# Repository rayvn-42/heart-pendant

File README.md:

## Heart Pendant
> A two part PCB, one used as a bracelet that senses heart pulses, and a pendant shaped as a heart that shows them

---

### What is Heart Pendant?
Its a small wearable made of two boards on a single PCB, joined by a break-away joint, The square half is a bracelet that measures the pulse with a heartbeat sensor.The heart-shaped half is a necklace pendant that shows each beat as a light animation moving smoothly around a ring of addressable LEDs. Once you snap the halves apart, each one works on its own and they talk to each other wirelessly.

### Why is Heart Pendant useful?
Its not really useful :), but its just fun and a reminder that each second your heart beats :) or something. I mean its just cool.

---

### How it works?
The bracelet's ESP32-C3 reads a heartbeat sensor module and detects each beat. It sends the beat to the pendant using the ESP-NOW protocol. Then the pendants ESP32 displays that heartbeat as a simple rotational animation using the addressable LEDs. Each half has its own LiPo battery, USB C port with a dedicated charge controller, and a 3v3 regulator, so both can be charged and used separately.

### Schematic

## So far
- [x] Schematic: ESP32 core, USB-C input, charger, regulator, power switch, battery sensing
- [x] Pulse sensor and LED ring
- [x] PCB layout
- [x] Quote Component & PCB + Stencil Order
- [x] Firmware

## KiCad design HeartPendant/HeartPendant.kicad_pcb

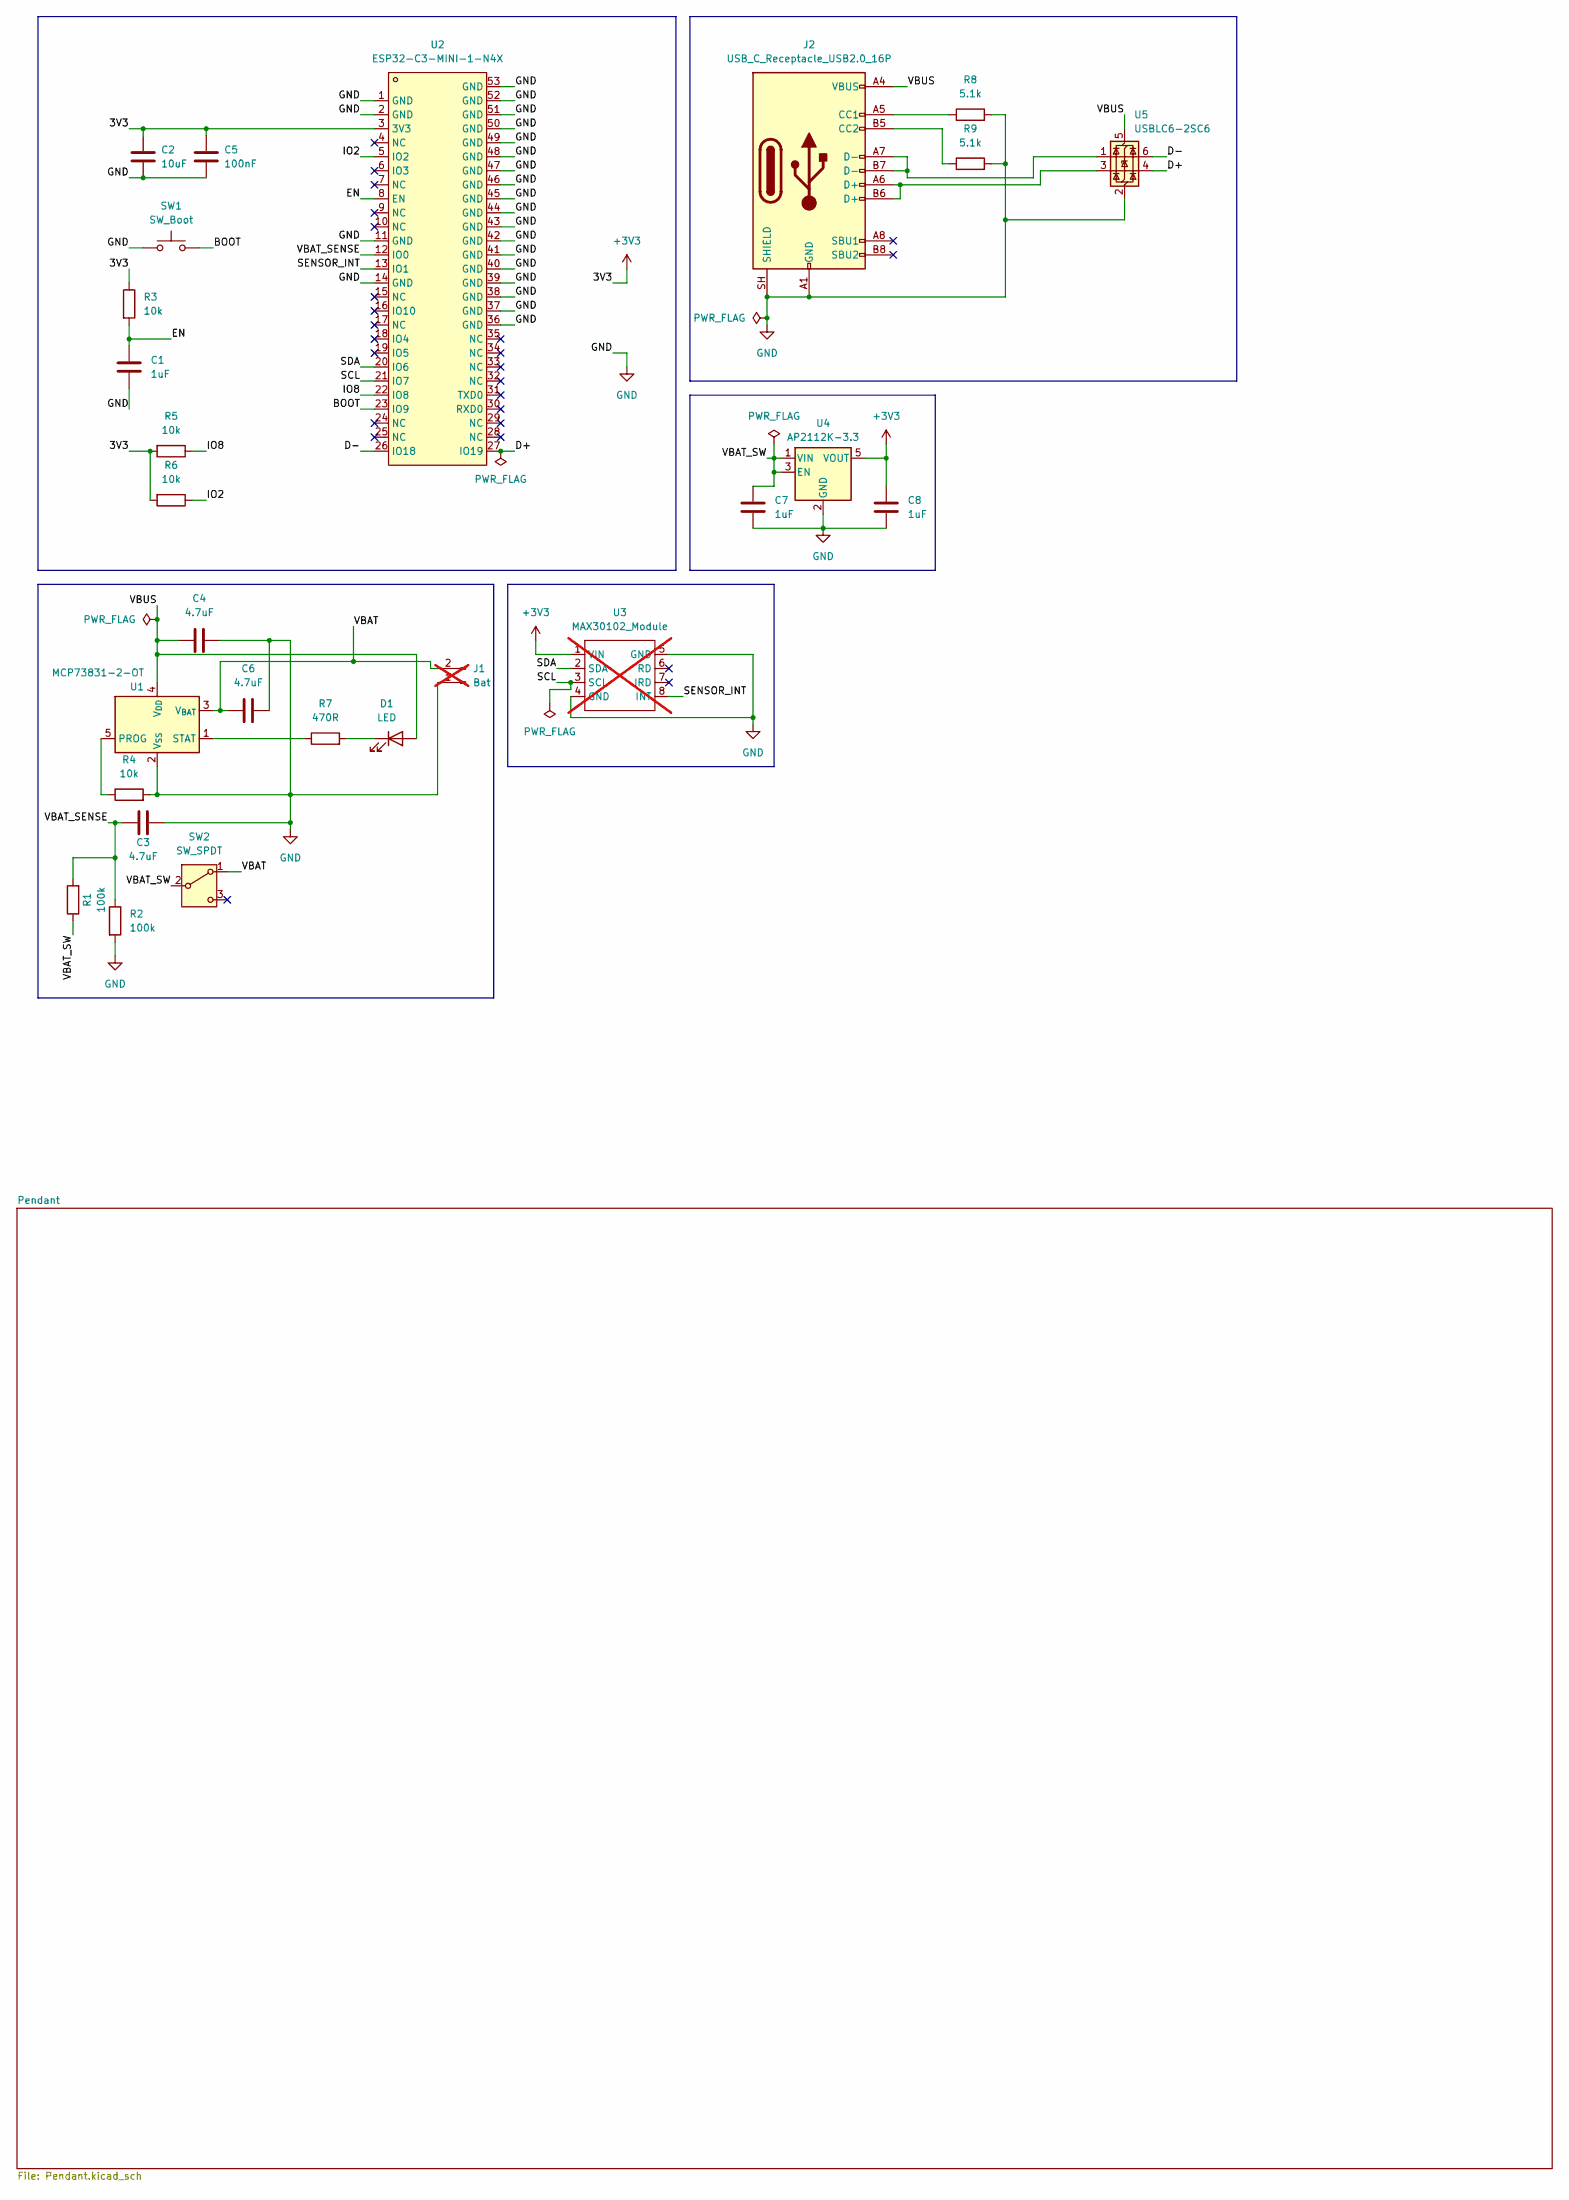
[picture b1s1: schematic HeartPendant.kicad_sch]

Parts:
C1, C7, C8: 1uF; C_0603_1608Metric; LCSC Part C1592
C2: 10uF; C_0805_2012Metric; LCSC Part C1713
C3, C4, C6: 4.7uF; C_0603_1608Metric; LCSC Part C1705
C5: 100nF; C_0603_1608Metric; LCSC Part C1590
D1: LED; LED_0603_1608Metric; LCSC Part C2286
J1: Bat; PinHeader_1x02_P2.54mm_Vertical; not fitted
J2: USB_C_Receptacle_USB2.0_16P; USB_C_Receptacle_HRO_TYPE-C-31-M-12; LCSC Part C165948
R1, R2: 100k; R_0603_1608Metric; LCSC Part C14675
R3, R4, R5, R6: 10k; R_0603_1608Metric; LCSC Part C15401
R7: 470R; R_0603_1608Metric; LCSC Part C23179
R8, R9: 5.1k; R_0603_1608Metric; LCSC Part C14677
SW1: SW_Boot; SW-SMD_4P-L4.2-W3.4-P2.15-LS5.2; LCSC Part C55200589
SW2: SW_SPDT; SW-TH_MSK12C02; LCSC Part C431540
U1: MCP73831-2-OT; SOT-23-5; LCSC Part C14879
U2: ESP32-C3-MINI-1-N4X; WIFIM-SMD_ESP32-C3-MINI-1; MPN ESP32-C3-MINI-1-N4X; LCSC Part C41349510
U3: MAX30102_Module; Max30102_Module; not fitted
U4: AP2112K-3.3; SOT-23-5; LCSC Part C51118
U5: USBLC6-2SC6; SOT-23-6; LCSC Part C7519

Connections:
+3V3: C2.2, C5.2, C8.1, R3.1, R5.2, R6.2, U2.3 (3V3), U3.1 (VIN), U4.5 (VOUT)
/BOOT: SW1.2, U2.23 (IO9)
/D+: U2.27 (IO19), U5.4 (I/O2)
/D-: U2.26 (IO18), U5.6 (I/O1)
/EN: C1.1, R3.2, U2.8 (EN)
/IO2: R6.1, U2.5 (IO2)
/IO8: R5.1, U2.22 (IO8)
/SCL: U2.21 (IO7), U3.3 (SCL)
/SDA: U2.20 (IO6), U3.2 (SDA)
/SENSOR_INT: U2.13 (IO1), U3.8 (INT)
/VBAT: C6.1, J1.2, SW2.1 (A), U1.3 (V_{BAT})
/VBAT_SENSE: C3.1, R1.2, R2.1, U2.12 (IO0)
/VBAT_SW: C7.1, R1.1, SW2.2 (B), U4.1 (VIN), U4.3 (EN)
/VBUS: C4.1, D1.2 (A), J2.A4 (VBUS), J2.A9 (VBUS), J2.B4 (VBUS), J2.B9 (VBUS), U1.4 (V_{DD}), U5.5 (VBUS)
GND: C1.2, C2.1, C3.2, C4.2, C5.1, C6.2, C7.2, C8.2, J1.1, J2.A1 (GND), J2.A12 (GND), J2.B1 (GND), J2.B12 (GND), J2.SH (SHIELD), R2.2, R4.2, R8.2, R9.2, SW1.1, U1.2 (V_{SS}), U2.1 (GND), U2.2 (GND), U2.11 (GND), U2.14 (GND), U2.36 (GND), U2.37 (GND), U2.38 (GND), U2.39 (GND), U2.40 (GND), U2.41 (GND), U2.42 (GND), U2.43 (GND), U2.44 (GND), U2.45 (GND), U2.46 (GND), U2.47 (GND), U2.48 (GND), U2.49 (GND), U2.50 (GND), U2.51 (GND), U2.52 (GND), U2.53 (GND), U3.4 (GND), U3.5 (GND), U4.2 (GND), U5.2 (GND)
unnamed: D1.1 (K), R7.2
unnamed: J2.A5 (CC1), R8.1
unnamed: J2.B5 (CC2), R9.1
unnamed: J2.A6 (D+), J2.B6 (D+), U5.3 (I/O2)
unnamed: J2.A7 (D-), J2.B7 (D-), U5.1 (I/O1)
unnamed: R4.1, U1.5 (PROG)
unnamed: R7.1, U1.1 (STAT)

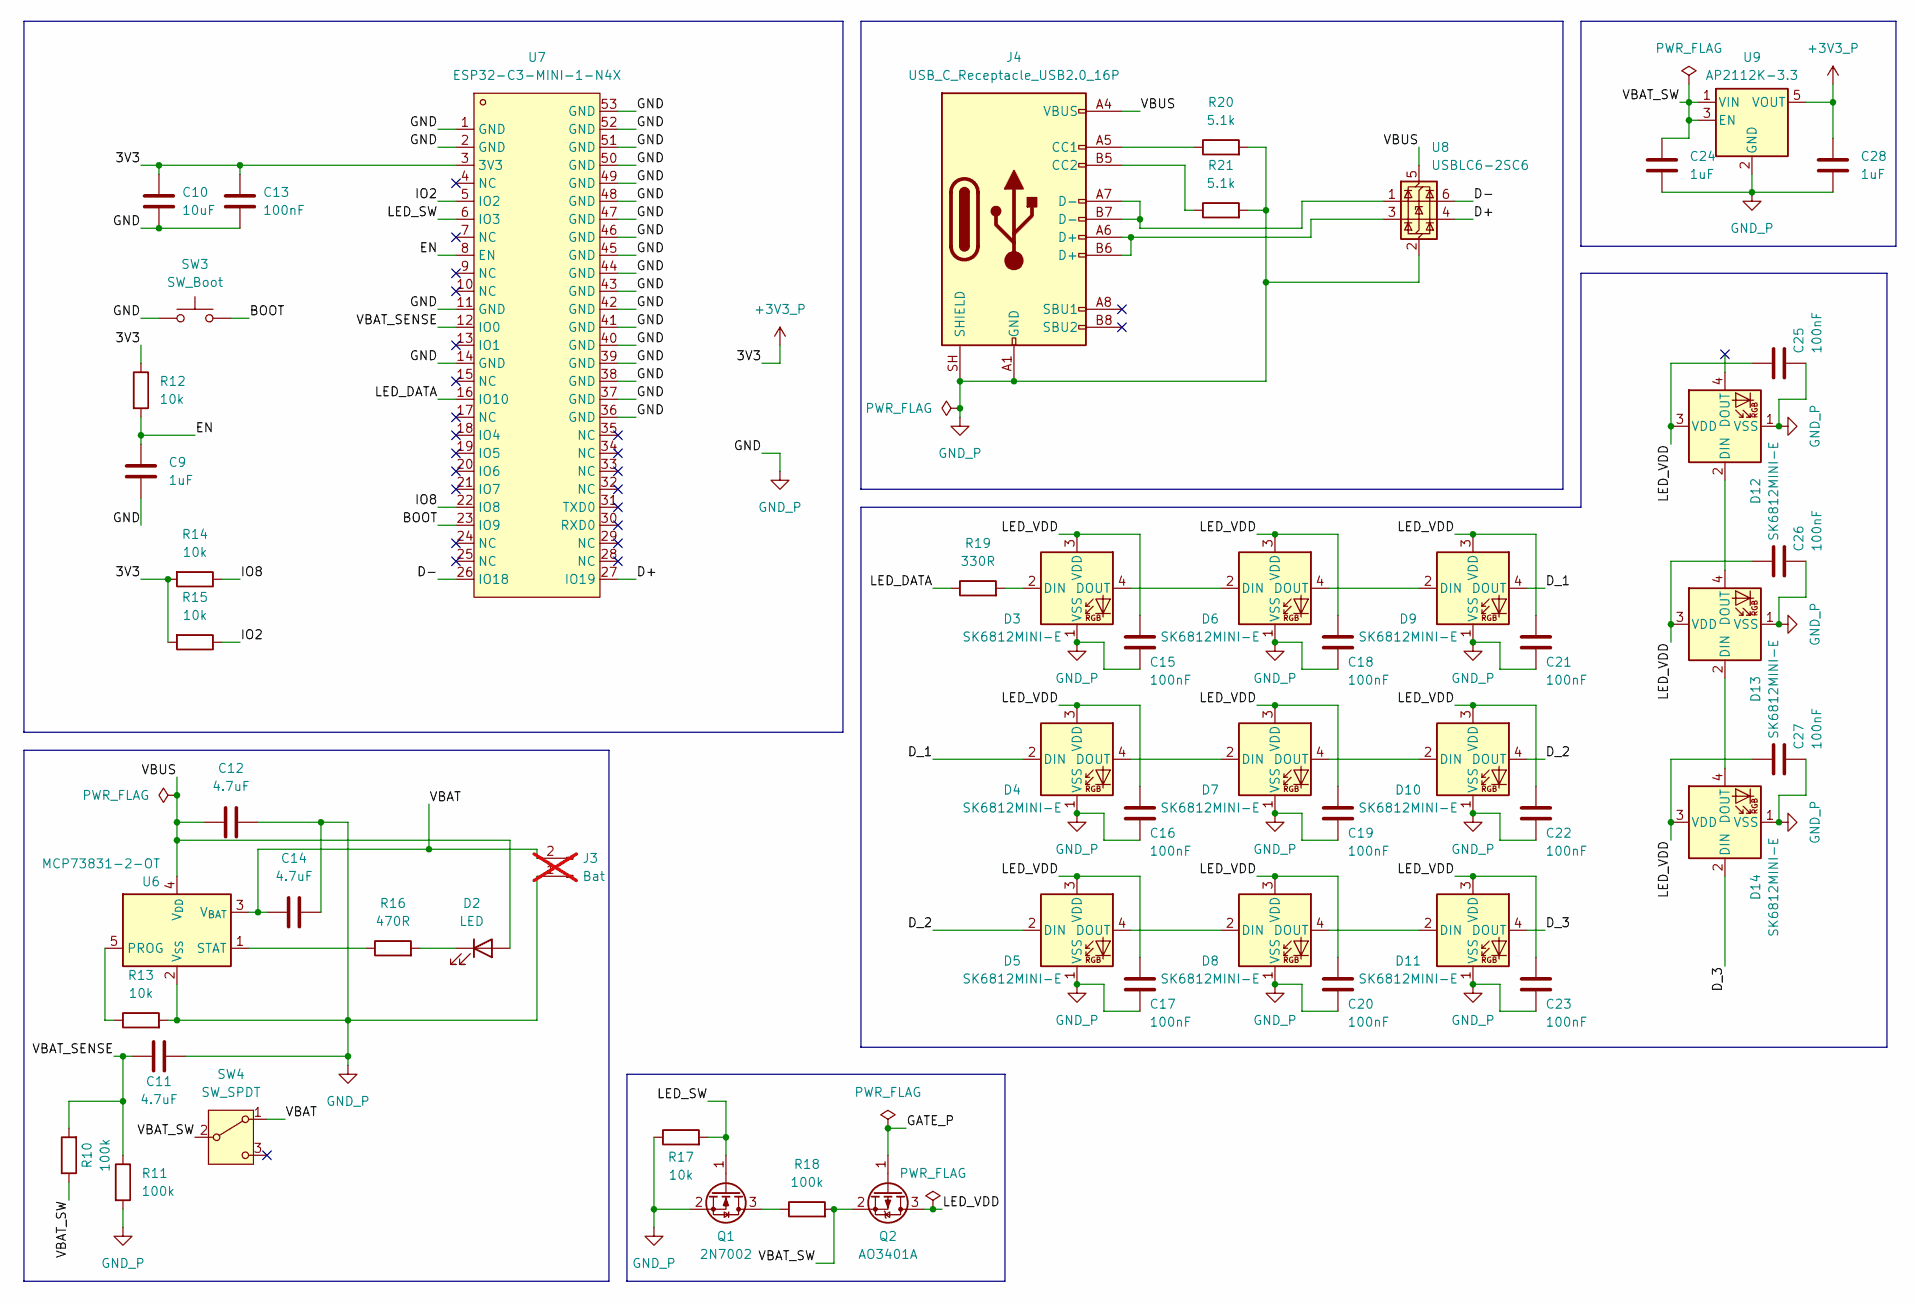
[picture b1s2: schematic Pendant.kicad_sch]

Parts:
C9, C24, C28: 1uF; C_0603_1608Metric; LCSC Part C1592
C10: 10uF; C_0805_2012Metric; LCSC Part C1713
C11, C12, C14: 4.7uF; C_0603_1608Metric; LCSC Part C1705
C13, C15, C16, C17, C18, C19, C20, C21, C22, C23, C25, C26, C27: 100nF; C_0603_1608Metric; LCSC Part C1590
D2: LED; LED_0603_1608Metric; LCSC Part C2286
D3, D4, D5, D6, D7, D8, D9, D10, D11, D12, D13, D14: SK6812MINI-E; LED_SK6812MINI-E_3.2x2.8mm_P1.5mm_ReverseMount; LCSC Part C5149201
J3: Bat; PinHeader_1x02_P2.54mm_Vertical; not fitted
J4: USB_C_Receptacle_USB2.0_16P; USB_C_Receptacle_HRO_TYPE-C-31-M-12; LCSC Part C165948
Q1: 2N7002; SOT-23; LCSC Part C8545
Q2: AO3401A; SOT-23; LCSC Part C478608
R10, R11, R18: 100k; R_0603_1608Metric; LCSC Part C14675
R12, R13, R14, R15, R17: 10k; R_0603_1608Metric; LCSC Part C15401
R16: 470R; R_0603_1608Metric; LCSC Part C23179
R19: 330R; R_0603_1608Metric; LCSC Part C22104
R20, R21: 5.1k; R_0603_1608Metric; LCSC Part C14677
SW3: SW_Boot; SW-SMD_4P-L4.2-W3.4-P2.15-LS5.2; LCSC Part C55200589
SW4: SW_SPDT; SW-TH_MSK12C02; LCSC Part C431540
U6: MCP73831-2-OT; SOT-23-5; LCSC Part C14879
U7: ESP32-C3-MINI-1-N4X; WIFIM-SMD_ESP32-C3-MINI-1; MPN ESP32-C3-MINI-1-N4X; LCSC Part C41349510
U8: USBLC6-2SC6; SOT-23-6; LCSC Part C7519
U9: AP2112K-3.3; SOT-23-5; LCSC Part C51118

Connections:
+3V3_P: C10.2, C13.2, C28.1, R12.1, R14.2, R15.2, U7.3 (3V3), U9.5 (VOUT)
/Pendant/BOOT: SW3.2, U7.23 (IO9)
/Pendant/D+: U7.27 (IO19), U8.4 (I/O2)
/Pendant/D-: U7.26 (IO18), U8.6 (I/O1)
/Pendant/D_1: D4.2 (DIN), D9.4 (DOUT)
/Pendant/D_2: D5.2 (DIN), D10.4 (DOUT)
/Pendant/D_3: D11.4 (DOUT), D14.2 (DIN)
/Pendant/EN: C9.1, R12.2, U7.8 (EN)
/Pendant/GATE_P: Q2.1 (G)
/Pendant/IO2: R15.1, U7.5 (IO2)
/Pendant/IO8: R14.1, U7.22 (IO8)
/Pendant/LED_DATA: R19.1, U7.16 (IO10)
/Pendant/LED_SW: Q1.1 (G), R17.2, U7.6 (IO3)
/Pendant/LED_VDD: C15.1, C16.1, C17.1, C18.1, C19.1, C20.1, C21.1, C22.1, C23.1, C25.1, C26.1, C27.1, D3.3 (VDD), D4.3 (VDD), D5.3 (VDD), D6.3 (VDD), D7.3 (VDD), D8.3 (VDD), D9.3 (VDD), D10.3 (VDD), D11.3 (VDD), D12.3 (VDD), D13.3 (VDD), D14.3 (VDD), Q2.3 (D)
/Pendant/VBAT: C14.1, J3.2, SW4.1 (A), U6.3 (V_{BAT})
/Pendant/VBAT_SENSE: C11.1, R10.2, R11.1, U7.12 (IO0)
/Pendant/VBAT_SW: C24.1, Q2.2 (S), R10.1, R18.2, SW4.2 (B), U9.1 (VIN), U9.3 (EN)
/Pendant/VBUS: C12.1, D2.2 (A), J4.A4 (VBUS), J4.A9 (VBUS), J4.B4 (VBUS), J4.B9 (VBUS), U6.4 (V_{DD}), U8.5 (VBUS)
GND_P: C9.2, C10.1, C11.2, C12.2, C13.1, C14.2, C15.2, C16.2, C17.2, C18.2, C19.2, C20.2, C21.2, C22.2, C23.2, C24.2, C25.2, C26.2, C27.2, C28.2, D3.1 (VSS), D4.1 (VSS), D5.1 (VSS), D6.1 (VSS), D7.1 (VSS), D8.1 (VSS), D9.1 (VSS), D10.1 (VSS), D11.1 (VSS), D12.1 (VSS), D13.1 (VSS), D14.1 (VSS), J3.1, J4.A1 (GND), J4.A12 (GND), J4.B1 (GND), J4.B12 (GND), J4.SH (SHIELD), Q1.2 (S), R11.2, R13.2, R17.1, R20.2, R21.2, SW3.1, U6.2 (V_{SS}), U7.1 (GND), U7.2 (GND), U7.11 (GND), U7.14 (GND), U7.36 (GND), U7.37 (GND), U7.38 (GND), U7.39 (GND), U7.40 (GND), U7.41 (GND), U7.42 (GND), U7.43 (GND), U7.44 (GND), U7.45 (GND), U7.46 (GND), U7.47 (GND), U7.48 (GND), U7.49 (GND), U7.50 (GND), U7.51 (GND), U7.52 (GND), U7.53 (GND), U8.2 (GND), U9.2 (GND)
unnamed: D2.1 (K), R16.2
unnamed: D3.2 (DIN), R19.2
unnamed: D3.4 (DOUT), D6.2 (DIN)
unnamed: D4.4 (DOUT), D7.2 (DIN)
unnamed: D5.4 (DOUT), D8.2 (DIN)
unnamed: D6.4 (DOUT), D9.2 (DIN)
unnamed: D7.4 (DOUT), D10.2 (DIN)
unnamed: D8.4 (DOUT), D11.2 (DIN)
unnamed: D12.2 (DIN), D13.4 (DOUT)
unnamed: D13.2 (DIN), D14.4 (DOUT)
unnamed: J4.A5 (CC1), R20.1
unnamed: J4.B5 (CC2), R21.1
unnamed: J4.A6 (D+), J4.B6 (D+), U8.3 (I/O2)
unnamed: J4.A7 (D-), J4.B7 (D-), U8.1 (I/O1)
unnamed: Q1.3 (D), R18.1
unnamed: R13.1, U6.5 (PROG)
unnamed: R16.1, U6.1 (STAT)

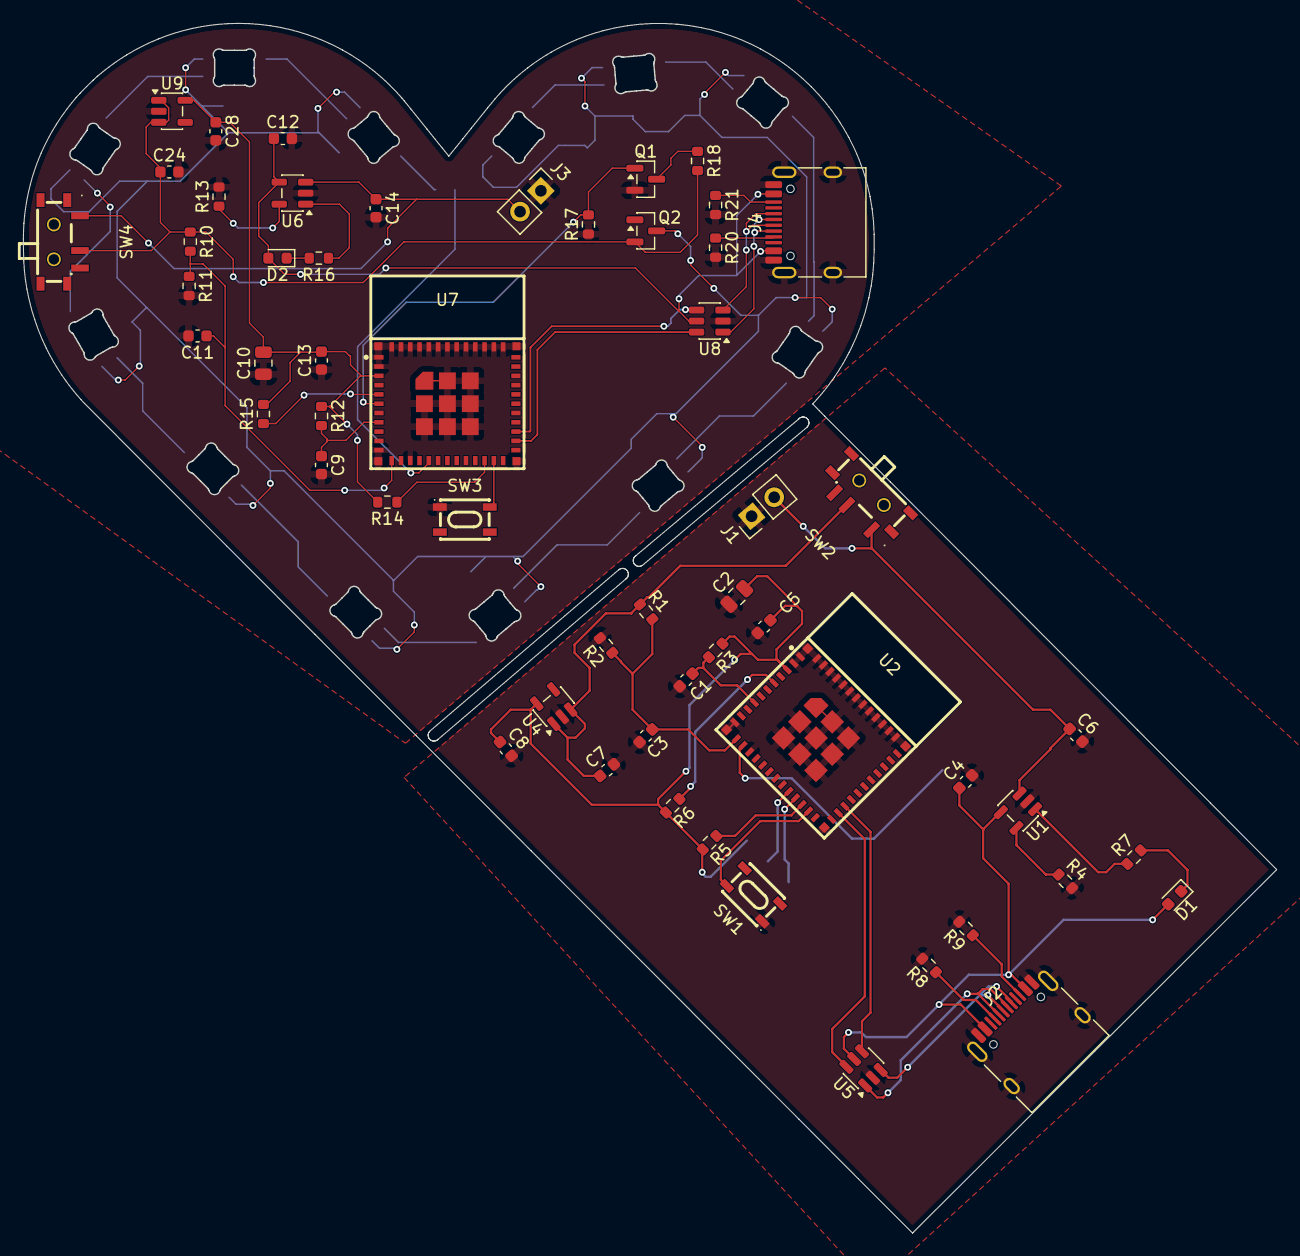
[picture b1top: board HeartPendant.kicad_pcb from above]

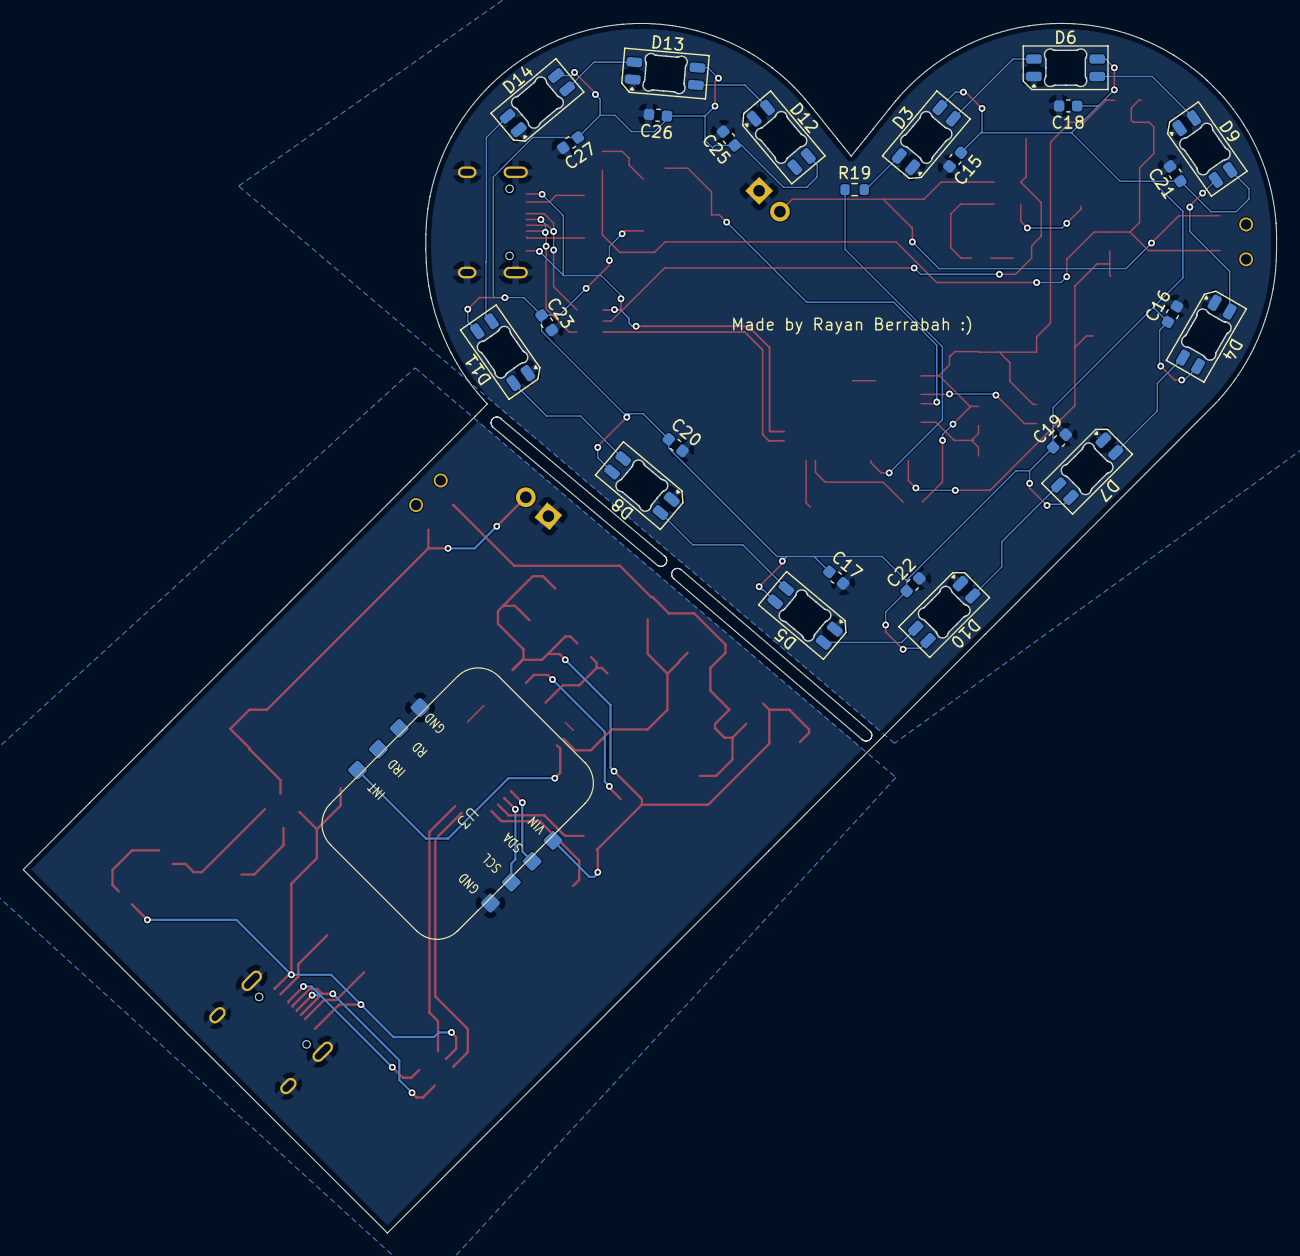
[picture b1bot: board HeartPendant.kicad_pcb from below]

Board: 2 copper layers, 108.0 x 104.2 mm, 82 parts (26 on the bottom side), 57 nets.

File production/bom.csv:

Designator,Footprint,Quantity,Value,LCSC Part #
"C1, C24, C28, C7, C8, C9",0603,6,1uF,C1592
"C10, C2",0805,2,10uF,C1713
"C11, C12, C14, C3, C4, C6",0603,6,4.7uF,C1705
"C13, C15, C16, C17, C18, C19, C20, C21, C22, C23, C25, C26, C27, C5",0603,14,100nF,C1590
"D1, D2",0603,2,LED,C2286
"D10, D11, D12, D13, D14, D3, D4, D5, D6, D7, D8, D9",LED_SK6812MINI-E_3.2x2.8mm_P1.5mm_ReverseMount,12,SK6812MINI-E,C5149201
"J2, J4",USB_C_Receptacle_HRO_TYPE-C-31-M-12,2,USB_C_Receptacle_USB2.0_16P,C165948
Q1,SOT-23,1,2N7002,C8545
Q2,SOT-23,1,AO3401A,C478608
"R1, R10, R11, R18, R2",0603,5,100k,C14675
"R12, R13, R14, R15, R17, R3, R4, R5, R6",0603,9,10k,C15401
"R16, R7",0603,2,470R,C23179
R19,0603,1,330R,C22104
"R20, R21, R8, R9",0603,4,5.1k,C14677
"SW1, SW3",SW-SMD_4P-L4.2-W3.4-P2.15-LS5.2,2,SW_Boot,C55200589
"SW2, SW4",SW-TH_MSK12C02,2,SW_SPDT,C431540
"U1, U6",SOT-23-5,2,MCP73831-2-OT,C14879
"U2, U7",WIFIM-SMD_ESP32-C3-MINI-1,2,ESP32-C3-MINI-1-N4X,C41349510
"U4, U9",SOT-23-5,2,AP2112K-3.3,C51118
"U5, U8",SOT-23-6,2,USBLC6-2SC6,C7519
